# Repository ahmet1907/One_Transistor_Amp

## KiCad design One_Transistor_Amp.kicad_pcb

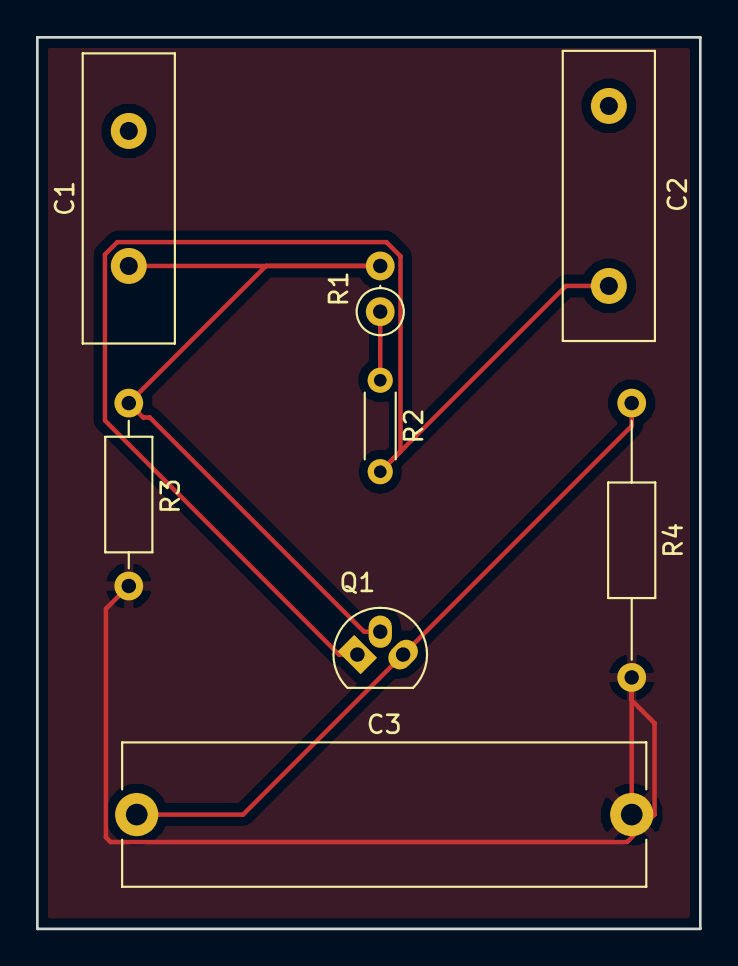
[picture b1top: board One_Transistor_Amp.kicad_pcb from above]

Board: 2 copper layers, 36.8 x 49.5 mm, 8 parts (0 on the bottom side), 5 nets.

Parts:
C1: 20uF; C_Disc_D16.0mm_W5.0mm_P7.50mm
C2: 20uF; C_Disc_D16.0mm_W5.0mm_P10.00mm
C3: 50uF; C_Rect_L29.0mm_W7.9mm_P27.50mm_MKT
Q1: BC548; TO-92_Molded_Narrow_Oval
R1: 22k; R_Axial_DIN0207_L6.3mm_D2.5mm_P2.54mm_Vertical
R2: 4.7k; R_Axial_DIN0204_L3.6mm_D1.6mm_P5.08mm_Horizontal
R3: 6.8k; R_Axial_DIN0207_L6.3mm_D2.5mm_P10.16mm_Horizontal
R4: 1.8k; R_Axial_DIN0207_L6.3mm_D2.5mm_P15.24mm_Horizontal

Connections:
+12V: R1.1, R2.1
GND: C3.2, R3.2, R4.2
unnamed: C1.1, Q1.2, R1.2, R3.1
unnamed: C2.2, Q1.1, R2.2
unnamed: C3.1, Q1.3, R4.1

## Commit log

2017-03-25 One_Transistor_Homework
2017-05-24 Single Transistor Amp
2017-05-27 One_Transistor_Amp
